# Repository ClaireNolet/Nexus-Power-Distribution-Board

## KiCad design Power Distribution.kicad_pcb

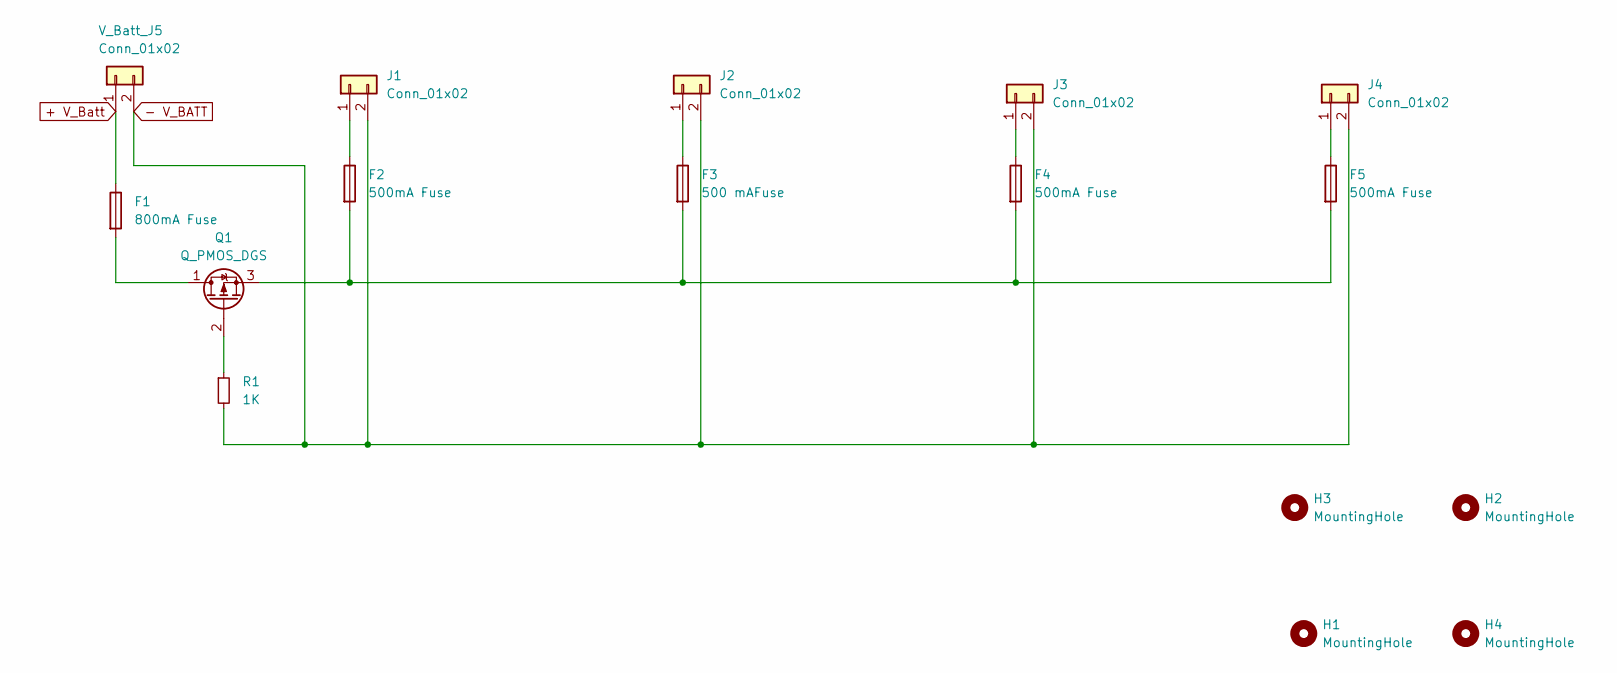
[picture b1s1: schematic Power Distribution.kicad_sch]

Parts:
F1: 800mA Fuse; Fuse_0603_1608Metric
F2, F4, F5: 500mA Fuse; Fuse_0603_1608Metric
F3: 500 mAFuse; Fuse_0603_1608Metric
H1, H2, H3, H4: MountingHole; MountingHole_3.2mm_M3
J1, J2, J3, J4: Conn_01x02; JST_XH_B2B-XH-A_1x02_P2.50mm_Vertical
Q1: Q_PMOS_DGS; SOT23_Standard
R1: 1K; R_0402_1005Metric
V_Batt_J5: Conn_01x02; JST_XH_B2B-XH-A_1x02_P2.50mm_Vertical

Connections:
+ V_Batt: F1.1, V_Batt_J5.1
- V_BATT: J1.2, J2.2, J3.2, J4.2, R1.2, V_Batt_J5.2
unnamed: F2.1, J1.1
unnamed: F3.1, J2.1
unnamed: F4.1, J3.1
unnamed: F5.1, J4.1
unnamed: F1.2, Q1.1 (D)
unnamed: Q1.2 (G), R1.1
unnamed: F2.2, F3.2, F4.2, F5.2, Q1.3 (S)

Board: 2 copper layers, 16 parts (0 on the bottom side), 9 nets, no tracks yet.

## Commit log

2025-07-20 Add files via upload
    Initial upload, sorry for the mess
2025-07-29 Add files via upload
    Changed MOSFET footprint to the one I found online, moved some traces accordingly. Moved traces with other components so that there was a 0.3mm minimum clearance between all components. Added Gerber 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
